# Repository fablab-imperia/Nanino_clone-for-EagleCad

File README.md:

This project is inspired by Johan von Kono's Nanino and forked from a Mariolukas Eagle clone by FabLab Imperia.

We made some minor moves and added some clearance for easier milling, added the groundplane, a prototyping zone like the Nanino, some reference values and the text. 
Also, we made a similar "mini" version without prototyping zone and reducing the Dimension layer.
Next releases will follow the original version number. Revision number will reflect further improvements.

This Design is still untested. Feel free to use and modify.

Links:
http://vonkonow.com/wordpress/2012/10/nanino-the-diy-friendly-arduino/
https://github.com/mariolukas/nanino-eagle
https://www.fablabs.io/fablabimperia

License:
CC-BY-NC-SA

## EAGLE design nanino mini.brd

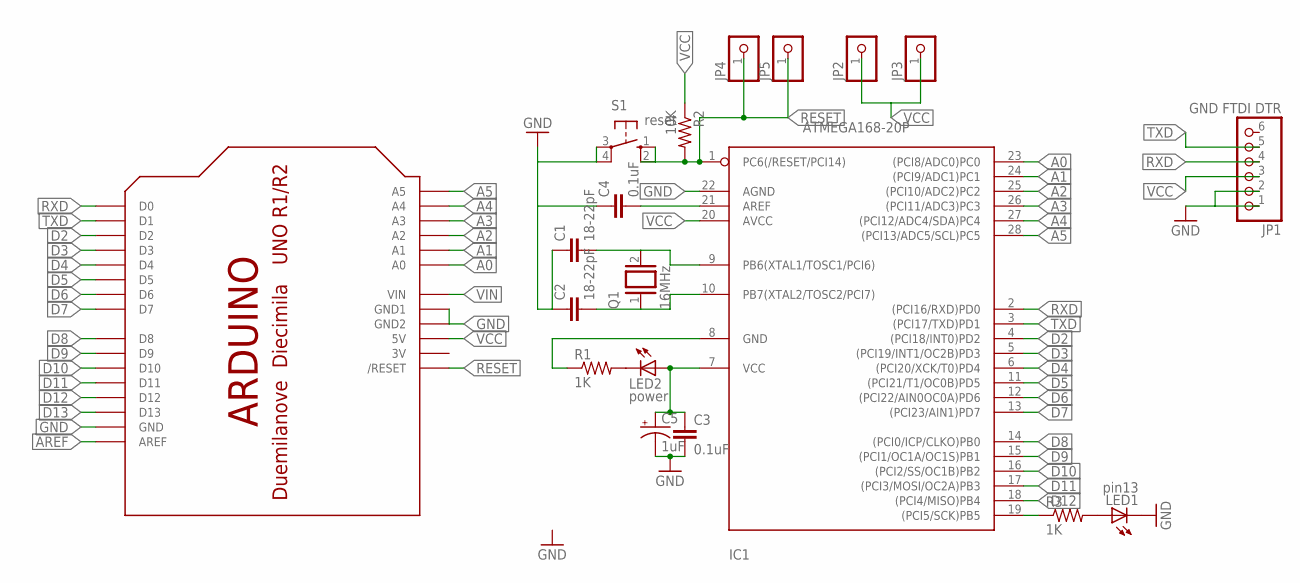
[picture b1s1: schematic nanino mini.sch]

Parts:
C1, C2: 18-22pF; C025-030X050
C3, C4: 0.1uF; C025-030X050
C5: 1uF; E2,5-6
IC1: ATMEGA168-20P; DIL28-3
JP1: GND FTDI DTR; 1X06
JP2, JP3, JP4, JP5: PINHD-1X1CB; 1X01-CLEANBIG
LED1: pin13; LED3MM
LED2: power; LED3MM
Q1: 16MHz; QS
R1, R3: 1K; 0207/10
R2: 10K; 0207/10
S1: reset; B3F-10XX
U$1: ARDUINOUNO; ARDUINO

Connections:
3V: U$1.3V
A0: IC1.23 ((PCI8/ADC0)PC0), U$1.A0
A1: IC1.24 ((PCI9/ADC1)PC1), U$1.A1
A2: IC1.25 ((PCI10/ADC2)PC2), U$1.A2
A3: IC1.26 ((PCI11/ADC3)PC3), U$1.A3
A4: IC1.27 ((PCI12/ADC4/SDA)PC4), U$1.A4
A5: IC1.28 ((PCI13/ADC5/SCL)PC5), U$1.A5
AREF: C4.2, IC1.21 (AREF), U$1.AREF
D2: IC1.4 ((PCI18/INT0)PD2), U$1.D2
D3: IC1.5 ((PCI19/INT1/OC2B)PD3), U$1.D3
D4: IC1.6 ((PCI20/XCK/T0)PD4), U$1.D4
D5: IC1.11 ((PCI21/T1/OC0B)PD5), U$1.D5
D6: IC1.12 ((PCI22/AIN0OC0A)PD6), U$1.D6
D7: IC1.13 ((PCI23/AIN1)PD7), U$1.D7
D8: IC1.14 ((PCI0/ICP/CLKO)PB0), U$1.D8
D9: IC1.15 ((PCI1/OC1A/OC1S)PB1), U$1.D9
D10: IC1.16 ((PCI2/SS/OC1B)PB2), U$1.D10
D11: IC1.17 ((PCI3/MOSI/OC2A)PB3), U$1.D11
D12: IC1.18 ((PCI4/MISO)PB4), U$1.D12
D13: IC1.19 ((PCI5/SCK)PB5), R3.1, U$1.D13
GND: C1.1, C2.1, C3.2, C4.1, C5.-, IC1.8 (GND), IC1.22 (AGND), JP1.1, JP1.2, LED1.K (C), R1.1, S1.3, S1.4 (P1), U$1.GND, U$1.GND1, U$1.GND2
unnamed: C1.2, IC1.9 (PB6(XTAL1/TOSC1/PCI6)), Q1.2
unnamed: C2.2, IC1.10 (PB7(XTAL2/TOSC2/PCI7)), Q1.1
unnamed: LED2.K (C), R1.2
unnamed: LED1.A, R3.2
RESET: IC1.1 (PC6(/RESET/PCI14)), JP4.1, JP5.1, R2.2, S1.1 (S), U$1.RESET (/RESET)
RXD: IC1.2 ((PCI16/RXD)PD0), JP1.4, U$1.D0
TXD: IC1.3 ((PCI17/TXD)PD1), JP1.5, U$1.D1
VCC: C3.1, C5.+, IC1.7 (VCC), IC1.20 (AVCC), JP1.3, JP2.1, JP3.1, LED2.A, R2.1, U$1.5V
VIN: U$1.VIN

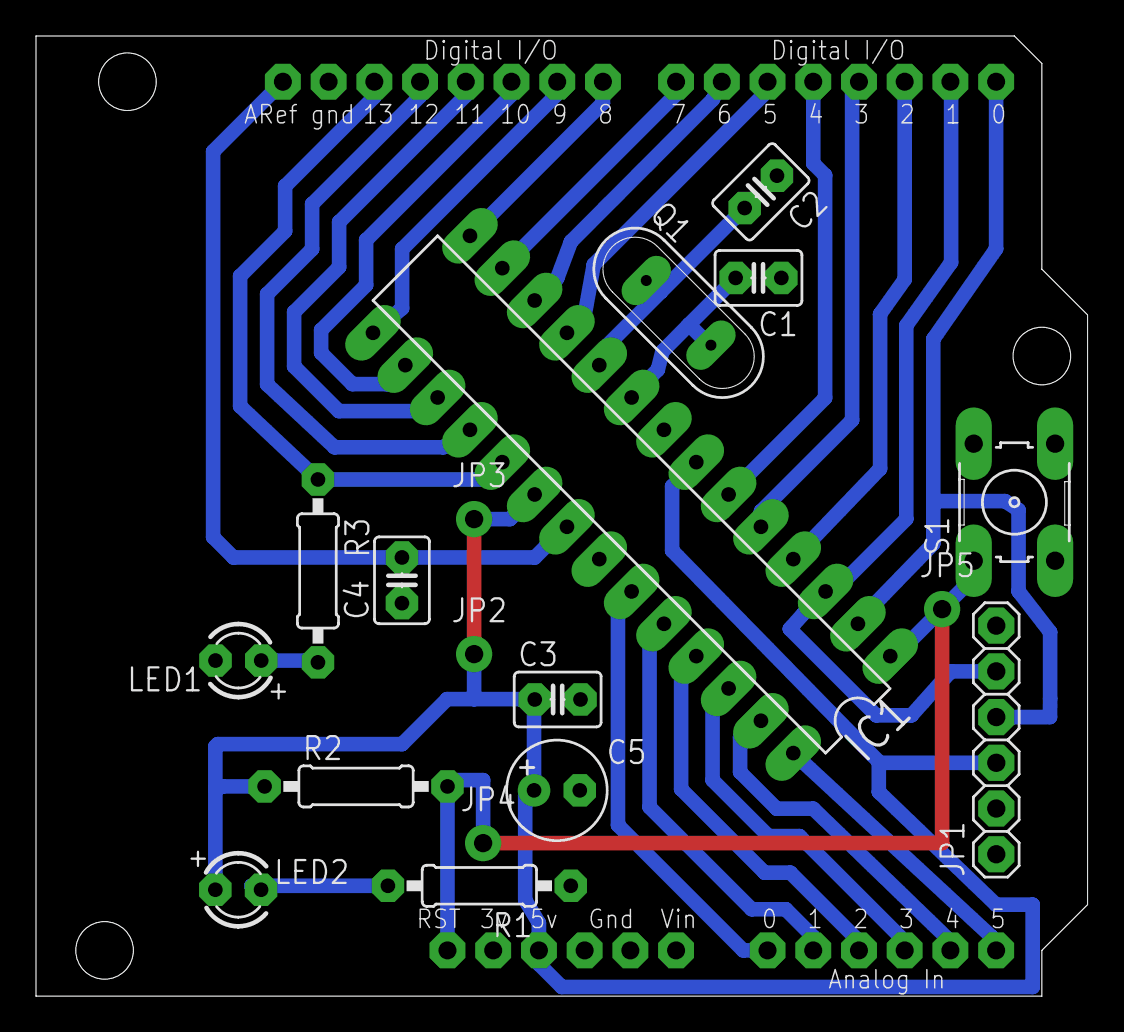
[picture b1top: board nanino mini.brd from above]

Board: 2 copper layers, 58.4 x 53.3 mm, 19 parts (0 on the bottom side), 28 nets.

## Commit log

2015-08-25 Fablab Imperia fork
    Some minor moves, added some clearance, added groundplane, prototyping
    zone like the Nanino, some reference values and the text
2015-08-25 Nanino mini
    Shorter board, without prototyping zone
